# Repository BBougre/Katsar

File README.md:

# Katsar | קצר

This project is the hebrew for "short" as I felt it was the right name for a gate to trigger converter.

This repository contains all the files necessary to build this little synth utility.
&nbsp;

## The theory
First comes the very simple schematics

&nbsp;

And then the simulated behavior using circuitJS

&nbsp;

## In the material world

All the separate components :

After soldering and assembly here is the final product :

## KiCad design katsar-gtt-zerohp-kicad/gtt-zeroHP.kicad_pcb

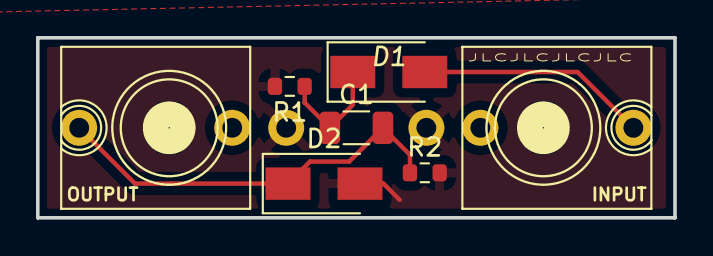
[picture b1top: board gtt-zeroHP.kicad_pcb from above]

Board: 2 copper layers, 35.4 x 10.0 mm, 7 parts (0 on the bottom side), 4 nets.

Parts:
C1: C; C_1206_3216Metric
D1, D2: D; D_SMA
J1: INPUT; AudioJack_WQP518MA
OUTPUT: OUTPUT; AudioJack_WQP518MA
R1: 330k; R_0603_1608Metric
R2: 100k; R_0603_1608Metric

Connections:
GND: D2.2 (A), J1.S (Sleeve), OUTPUT.S (Sleeve), R1.2, R2.2
unnamed: C1.1, D1.1 (K), R1.1
unnamed: D1.2 (A), J1.T (Tip)
unnamed: C1.2, D2.1 (K), OUTPUT.T (Tip), R2.1

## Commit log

2023-08-24 Files added
2023-08-24 Added photos
    pic_1 is the separate PCB and component, pic_2 is the final product.
2023-08-24 added .gitignore
2023-08-24 readme update
2023-08-24 pictures of schematics and simulation added
